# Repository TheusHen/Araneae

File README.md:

<table align="center">
<tr>
<td>

<h1>Araneae</h1>

</td>
<td>

</td>
</tr>
</table>

<h3 align="center">
Your network should answer to you, not report on you.
</h3>

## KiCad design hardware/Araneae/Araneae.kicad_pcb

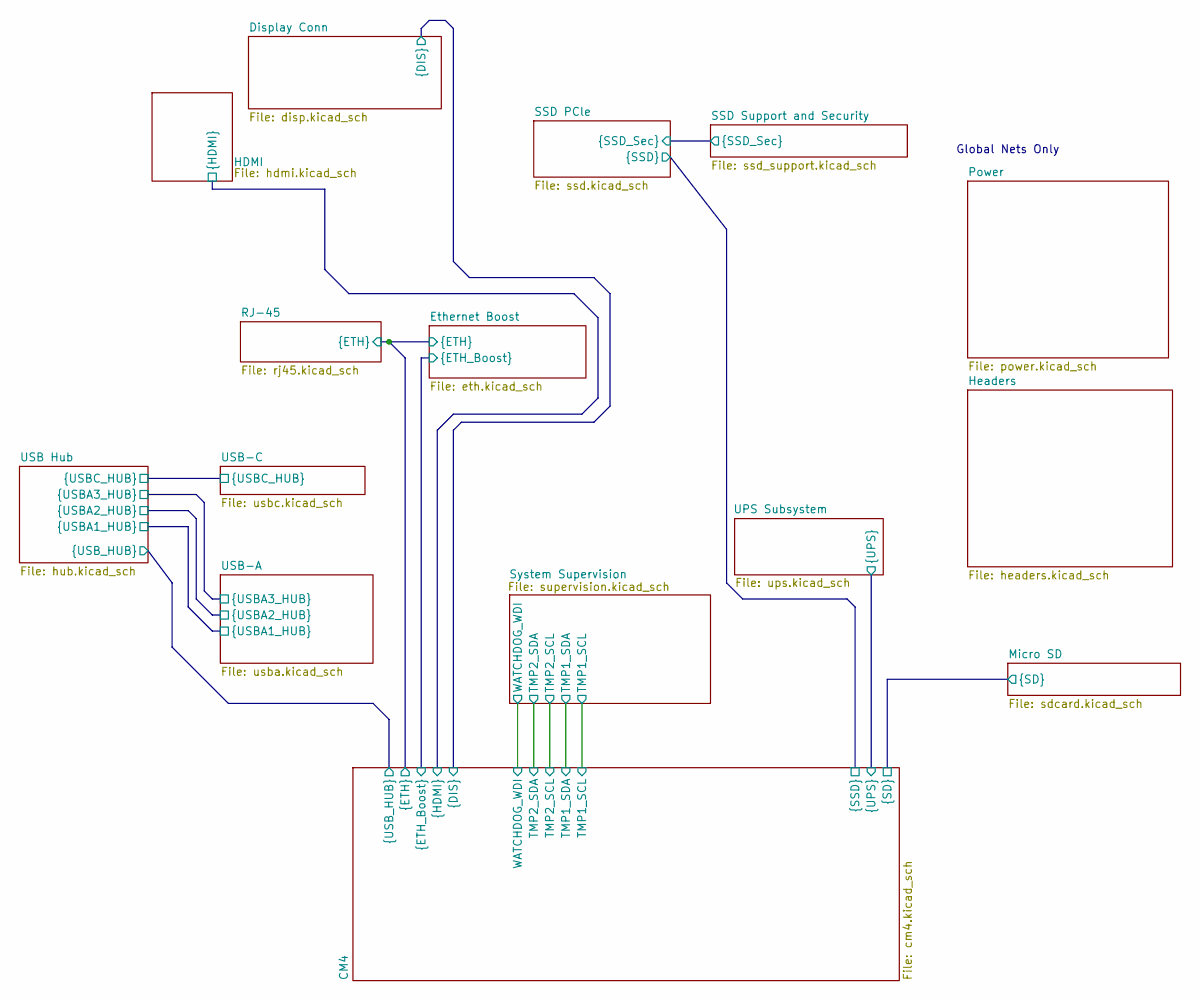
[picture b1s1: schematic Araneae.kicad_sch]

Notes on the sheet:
Global Nets Only

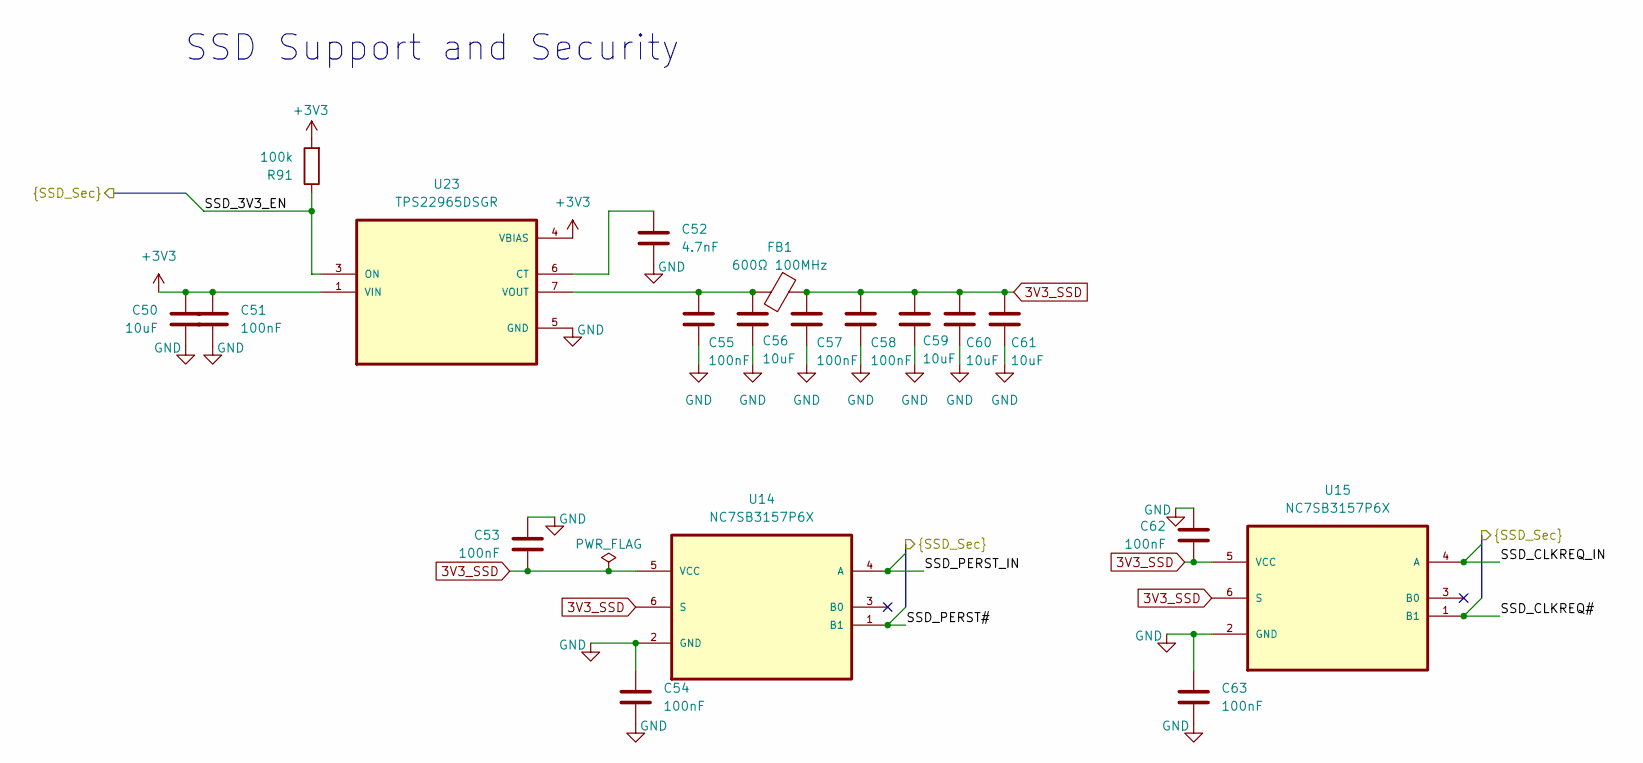
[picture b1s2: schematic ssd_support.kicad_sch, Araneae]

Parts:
C50, C56, C59: 10uF; C_0603_1608Metric
C51, C57, C62: 100nF; C_0805_2012Metric
C52: 4.7nF; C_0603_1608Metric
C53, C54, C55, C58, C63: 100nF; C_0603_1608Metric
C60, C61: 10uF; C_0805_2012Metric
FB1: 600Ω 100MHz; L_0805_2012Metric
R91: 100k; R_0603_1608Metric
U14, U15: NC7SB3157P6X; SOT65P210X110-6N; MPN NC7SB3157P6X
U23: TPS22965DSGR; SON50P200X200X80-9N

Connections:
3V3_SSD: C53.2, C57.1, C58.1, C59.1, C60.1, C61.1, C62.2, FB1.1, U14.5 (VCC), U14.6 (S), U15.5 (VCC), U15.6 (S); also elsewhere on the board
+3V3: C50.1, C51.1, R91.2, U23.1 (VIN), U23.2 (VIN), U23.4 (VBIAS); also elsewhere on the board
/SSD PCle/SSD_3V3_EN: R91.1, U23.3 (ON)
/SSD PCle/SSD_CLKREQ#: U15.1 (B1); also elsewhere on the board
/SSD PCle/SSD_CLKREQ_IN: U15.4 (A)
/SSD PCle/SSD_PERST#: U14.1 (B1); also elsewhere on the board
/SSD PCle/SSD_PERST_IN: U14.4 (A)
GND: C50.2, C51.2, C52.2, C53.1, C54.1, C54.2, C55.2, C56.2, C57.2, C58.2, C59.2, C60.2, C61.2, C62.1, C63.1, C63.2, U14.2 (GND), U15.2 (GND), U23.5 (GND), U23.9 (GND), U23.9_1 (GND), U23.9_2 (GND); also elsewhere on the board
unnamed: C55.1, C56.1, FB1.2, U23.7 (VOUT), U23.8 (VOUT)
unnamed: C52.1, U23.6 (CT)

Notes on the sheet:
SSD Support and Security

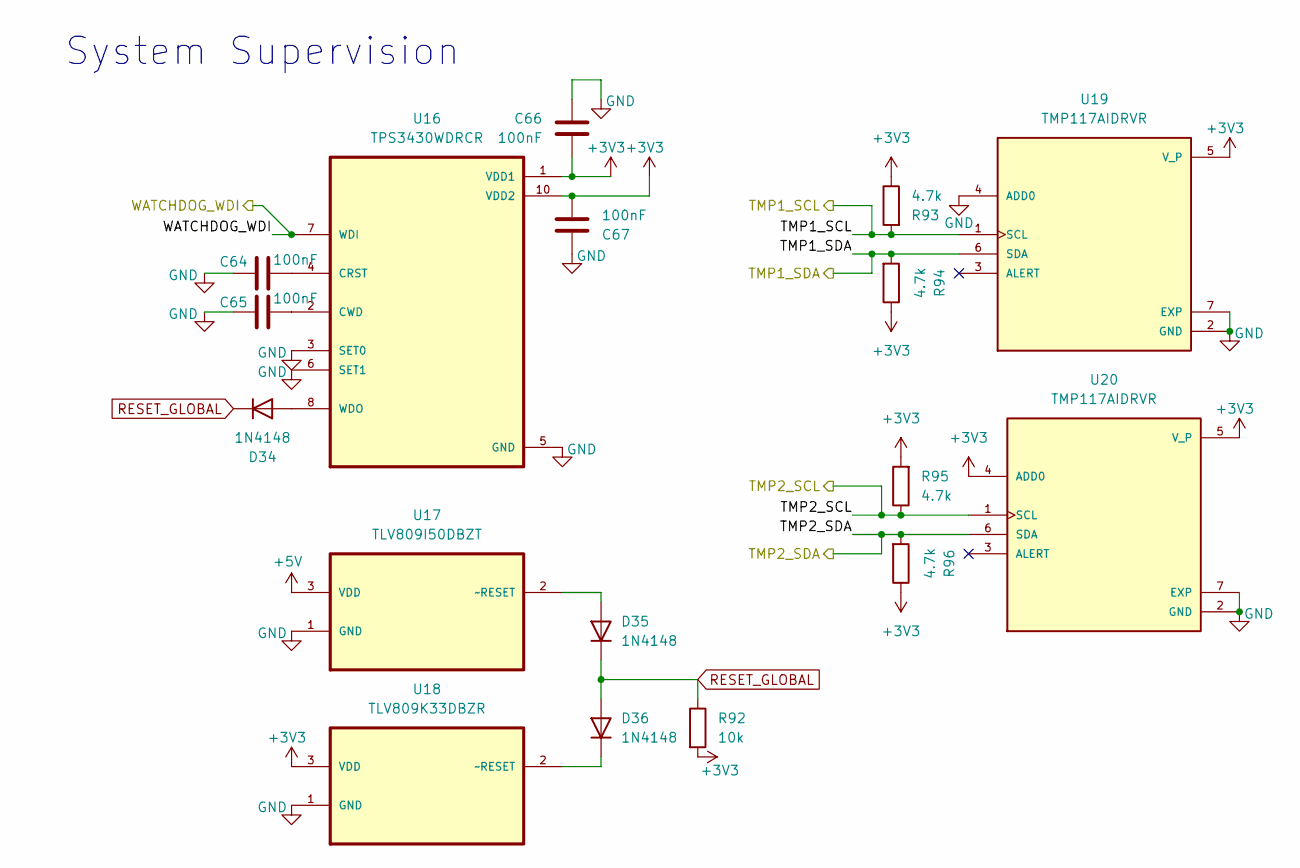
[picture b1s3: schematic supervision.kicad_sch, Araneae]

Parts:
C64, C65, C66, C67: 100nF; C_0603_1608Metric
D34, D35, D36: 1N4148; D_DO-35_SOD27_P7.62mm_Horizontal
R92: 10k; R_0603_1608Metric
R93, R94, R95, R96: 4.7k; R_0603_1608Metric
U16: TPS3430WDRCR; VREG_V62_16624-01YE
U17: TLV809I50DBZT; SOT95P280X145-3N; MPN TLV809I50DBZT
U18: TLV809K33DBZR; SOT95P280X145-3N; MPN TLV809K33DBZR
U19, U20: TMP117AIDRVR; SON65P200X200X80-7N; PARTREV B

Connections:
+3V3: C66.1, C67.1, R92.2, R93.1, R94.1, R95.2, R96.1, U16.1 (VDD1), U16.10 (VDD2), U18.3 (VDD), U19.5 (V_P), U20.4 (ADD0), U20.5 (V_P); also elsewhere on the board
+5V: U17.3 (VDD); also elsewhere on the board
/CM4/WATCHDOG_WDI: U16.7 (WDI); also elsewhere on the board
EXT_I2C_SCL: R93.2, R95.1, U19.1 (SCL), U20.1 (SCL); also elsewhere on the board
EXT_I2C_SDA: R94.2, R96.2, U19.6 (SDA), U20.6 (SDA); also elsewhere on the board
GND: C64.2, C65.2, C66.2, C67.2, U16.3 (SET0), U16.5 (GND), U16.6 (SET1), U17.1 (GND), U18.1 (GND), U19.2 (GND), U19.4 (ADD0), U19.7 (EXP), U20.2 (GND), U20.7 (EXP); also elsewhere on the board
unnamed: D34.2 (A), U16.8 (WDO)
unnamed: D35.2 (A), U17.2 (~RESET)
unnamed: D36.1 (K), U18.2 (~RESET)
unnamed: C64.1, U16.4 (CRST)
unnamed: C65.1, U16.2 (CWD)
RESET_GLOBAL: D34.1 (K), D35.1 (K), D36.2 (A), R92.1; also elsewhere on the board

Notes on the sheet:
System Supervision

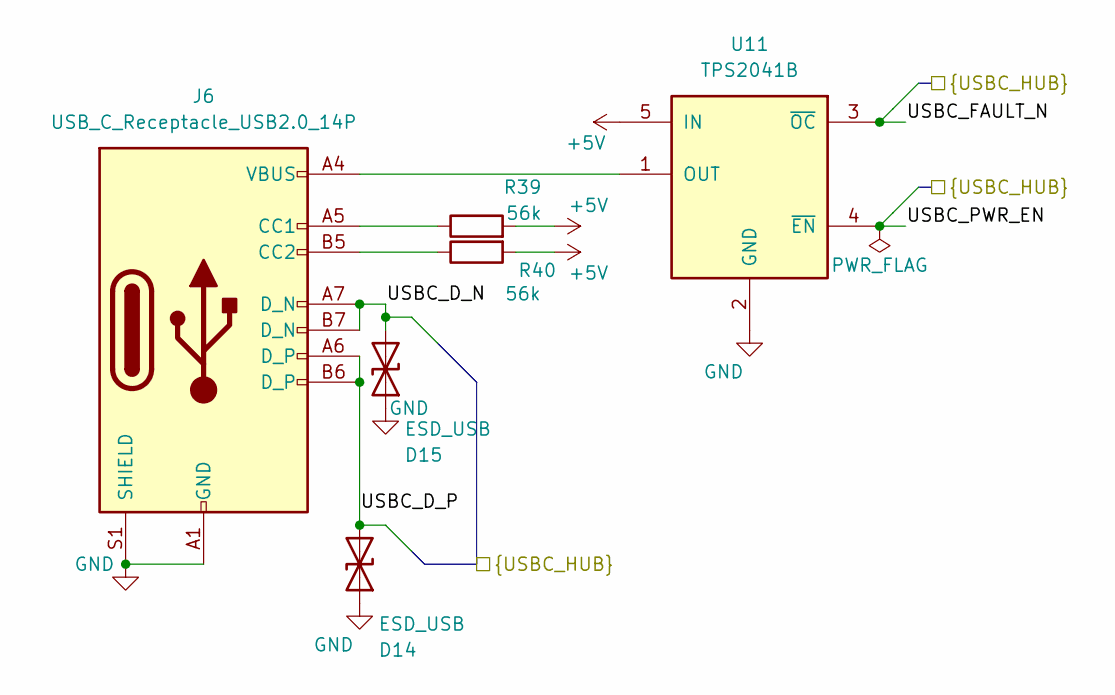
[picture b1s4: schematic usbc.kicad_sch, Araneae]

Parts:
D14, D15: ESD_USB; D_SOD-323
J6: USB_C_Receptacle_USB2.0_14P; USB_C_Receptacle_HRO_TYPE-C-31-M-12
R39, R40: 56k; R_0603_1608Metric
U11: TPS2041B; SOT-23-5

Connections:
+5V: R39.2, R40.2, U11.5 (IN); also elsewhere on the board
/USB Hub/USBC_D_N: D15.2 (A2), J6.A7 (D_N), J6.B7 (D_N); also elsewhere on the board
/USB Hub/USBC_D_P: D14.2 (A2), J6.A6 (D_P), J6.B6 (D_P); also elsewhere on the board
/USB Hub/USBC_FAULT_N: U11.3 (~OC); also elsewhere on the board
/USB Hub/USBC_PWR_EN: U11.4 (~EN); also elsewhere on the board
GND: D14.1 (A1), D15.1 (A1), J6.A1 (GND), J6.A12 (GND), J6.B1 (GND), J6.B12 (GND), J6.S1 (SHIELD), U11.2 (GND); also elsewhere on the board
unnamed: J6.A5 (CC1), R39.1
unnamed: J6.B5 (CC2), R40.1
unnamed: J6.A4 (VBUS), J6.A9 (VBUS), J6.B4 (VBUS), J6.B9 (VBUS), U11.1 (OUT)

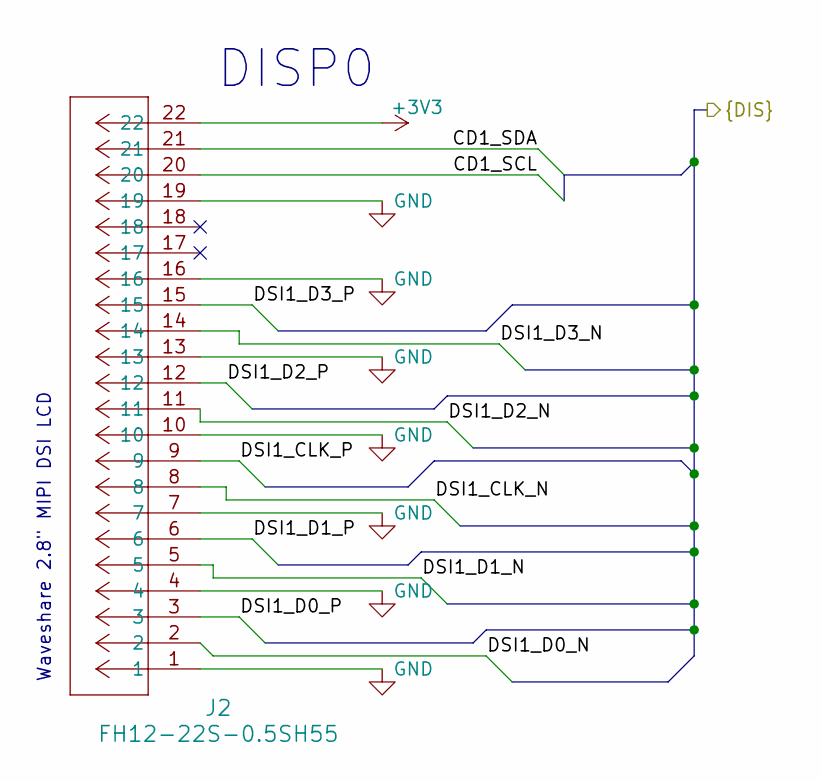
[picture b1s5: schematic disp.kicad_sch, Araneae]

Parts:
J2: FH12-22S-0.5SH55; CONN_FH12-22S-0.5SH55_HIR

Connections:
+3V3: J2.22; also elsewhere on the board
/CM4/CD1_SCL: J2.20; also elsewhere on the board
/CM4/CD1_SDA: J2.21; also elsewhere on the board
/CM4/DSI1_CLK_N: J2.8; also elsewhere on the board
/CM4/DSI1_CLK_P: J2.9; also elsewhere on the board
/CM4/DSI1_D0_N: J2.2; also elsewhere on the board
/CM4/DSI1_D0_P: J2.3; also elsewhere on the board
/CM4/DSI1_D1_N: J2.5; also elsewhere on the board
/CM4/DSI1_D1_P: J2.6; also elsewhere on the board
/CM4/DSI1_D2_N: J2.11; also elsewhere on the board
/CM4/DSI1_D2_P: J2.12; also elsewhere on the board
/CM4/DSI1_D3_N: J2.14; also elsewhere on the board
/CM4/DSI1_D3_P: J2.15; also elsewhere on the board
GND: J2.1, J2.4, J2.7, J2.10, J2.13, J2.16, J2.19; also elsewhere on the board

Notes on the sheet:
DISP0
Waveshare 2.8" MIPI DSI LCD

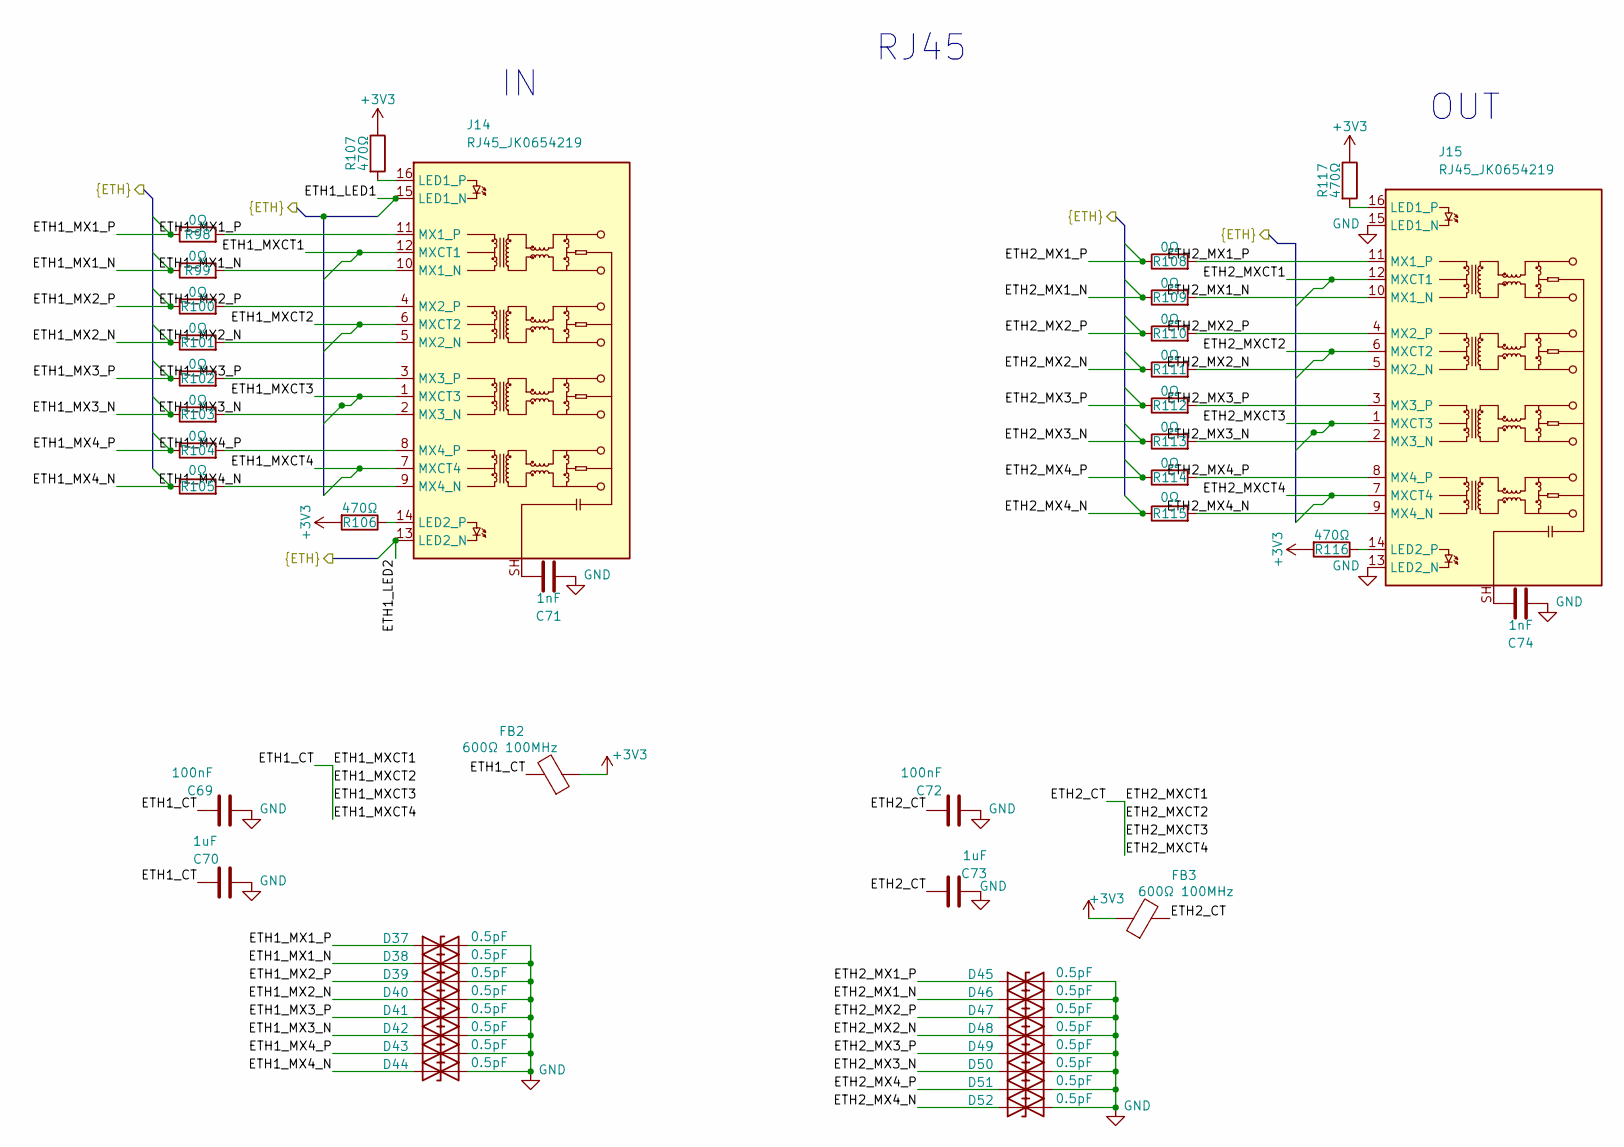
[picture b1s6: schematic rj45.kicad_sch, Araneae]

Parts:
C69: 100nF; C_0805_2012Metric
C70, C73: 1uF; C_0603_1608Metric
C71, C74: 1nF; C_0603_1608Metric
C72: 100nF; C_0603_1608Metric
D37, D38, D39, D40, D41, D42, D43, D44, D45, D46, D47, D48, D49, D50, D51, D52: 0.5pF; D_SOD-523
FB2, FB3: 600Ω 100MHz; L_0805_2012Metric
J14, J15: RJ45_JK0654219; RJ45_Pulse_JK0654219NL_Horizontal
R98, R99, R100, R101, R102, R103, R104, R105, R108, R109, R110, R111, R112, R113, R114, R115: 0Ω; R_0603_1608Metric
R106, R107, R116, R117: 470Ω; R_0603_1608Metric

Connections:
+3V3: FB2.1, FB3.1, R106.2, R107.1, R116.2, R117.1; also elsewhere on the board
/CM4/ETH1_LED1: J14.15 (LED1_N); also elsewhere on the board
/CM4/ETH1_LED2: J14.13 (LED2_N); also elsewhere on the board
/CM4/ETH1_MX1_N: D38.1 (A1), J14.10 (MX1_N), R99.1, R99.2; also elsewhere on the board
/CM4/ETH1_MX1_P: D37.1 (A1), J14.11 (MX1_P), R98.1, R98.2; also elsewhere on the board
/CM4/ETH1_MX2_N: D40.1 (A1), J14.5 (MX2_N), R101.1, R101.2; also elsewhere on the board
/CM4/ETH1_MX2_P: D39.1 (A1), J14.4 (MX2_P), R100.1, R100.2; also elsewhere on the board
/CM4/ETH1_MX3_N: D42.1 (A1), J14.2 (MX3_N), R103.1, R103.2; also elsewhere on the board
/CM4/ETH1_MX3_P: D41.1 (A1), J14.3 (MX3_P), R102.1, R102.2; also elsewhere on the board
/CM4/ETH1_MX4_N: D44.1 (A1), J14.9 (MX4_N), R105.1, R105.2; also elsewhere on the board
/CM4/ETH1_MX4_P: D43.1 (A1), J14.8 (MX4_P), R104.1, R104.2; also elsewhere on the board
/CM4/ETH1_MXCT4: C69.1, C70.2, FB2.2, J14.1 (MXCT3), J14.6 (MXCT2), J14.7 (MXCT4), J14.12 (MXCT1)
/CM4/ETH2_MX1_N: D46.1 (A1), J15.10 (MX1_N), R109.1, R109.2; also elsewhere on the board
/CM4/ETH2_MX1_P: D45.1 (A1), J15.11 (MX1_P), R108.1, R108.2; also elsewhere on the board
/CM4/ETH2_MX2_N: D48.1 (A1), J15.5 (MX2_N), R111.1, R111.2; also elsewhere on the board
/CM4/ETH2_MX2_P: D47.1 (A1), J15.4 (MX2_P), R110.1, R110.2; also elsewhere on the board
/CM4/ETH2_MX3_N: D50.1 (A1), J15.2 (MX3_N), R113.1, R113.2; also elsewhere on the board
/CM4/ETH2_MX3_P: D49.1 (A1), J15.3 (MX3_P), R112.1, R112.2; also elsewhere on the board
/CM4/ETH2_MX4_N: D52.1 (A1), J15.9 (MX4_N), R115.1, R115.2; also elsewhere on the board
/CM4/ETH2_MX4_P: D51.1 (A1), J15.8 (MX4_P), R114.1, R114.2; also elsewhere on the board
/CM4/ETH2_MXCT4: C72.1, C73.1, FB3.2, J15.1 (MXCT3), J15.6 (MXCT2), J15.7 (MXCT4), J15.12 (MXCT1)
GND: C69.2, C70.1, C71.2, C72.2, C73.2, C74.2, D37.2 (A2), D38.2 (A2), D39.2 (A2), D40.2 (A2), D41.2 (A2), D42.2 (A2), D43.2 (A2), D44.2 (A2), D45.2 (A2), D46.2 (A2), D47.2 (A2), D48.2 (A2), D49.2 (A2), D50.2 (A2), D51.2 (A2), D52.2 (A2), J15.13 (LED2_N), J15.15 (LED1_N); also elsewhere on the board
unnamed: C71.1, J14.SH
unnamed: C74.1, J15.SH
unnamed: J14.16 (LED1_P), R107.2
unnamed: J14.14 (LED2_P), R106.1
unnamed: J15.16 (LED1_P), R117.2
unnamed: J15.14 (LED2_P), R116.1

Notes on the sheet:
OUT
RJ45

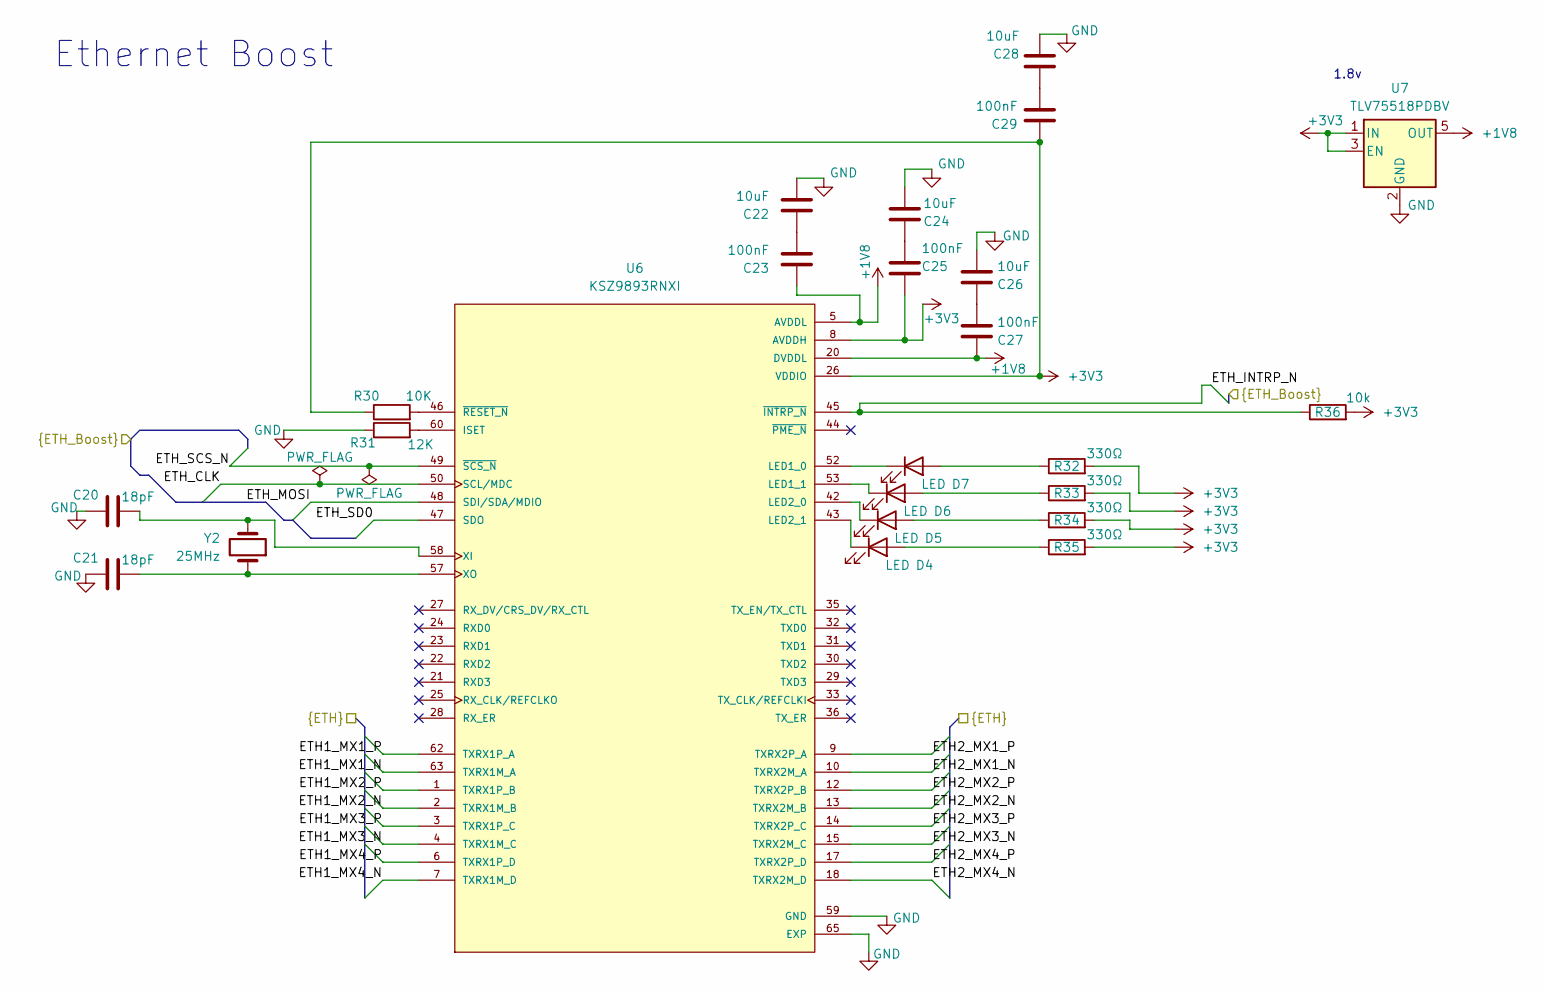
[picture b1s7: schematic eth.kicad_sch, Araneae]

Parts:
C20, C21: 18pF; C_0603_1608Metric
C22, C24, C26, C28: 10uF; C_0805_2012Metric
C23, C25, C27, C29: 100nF; C_0603_1608Metric
D4, D5, D6, D7: LED; LED_0805_2012Metric
R30: 10K; R_0603_1608Metric
R31: 12K; R_0603_1608Metric
R32, R33, R34, R35: 330Ω; R_0603_1608Metric
R36: 10k; R_0603_1608Metric
U6: KSZ9893RNXI; QFN40P800X800X90-65N; PARTREV C
U7: TLV75518PDBV; SOT-23-5
Y2: 25MHz; Crystal_SMD_3225-4Pin_3.2x2.5mm

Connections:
+1V8: C23.1, C27.1, U6.5 (AVDDL), U6.11 (AVDDL), U6.16 (AVDDL), U6.20 (DVDDL), U6.34 (DVDDL), U6.37 (DVDDL), U6.41 (DVDDL), U6.51 (DVDDL), U6.55 (DVDDL), U6.56 (AVDDL), U6.64 (AVDDL), U7.5 (OUT); also elsewhere on the board
+3V3: C25.1, C29.1, R30.1, R32.2, R33.2, R34.2, R35.2, R36.2, U6.8 (AVDDH), U6.19 (AVDDH), U6.26 (VDDIO), U6.38 (VDDIO), U6.54 (VDDIO), U6.61 (AVDDH), U7.1 (IN), U7.3 (EN); also elsewhere on the board
/CM4/ETH1_MX1_N: U6.63 (TXRX1M_A); also elsewhere on the board
/CM4/ETH1_MX1_P: U6.62 (TXRX1P_A); also elsewhere on the board
/CM4/ETH1_MX2_N: U6.2 (TXRX1M_B); also elsewhere on the board
/CM4/ETH1_MX2_P: U6.1 (TXRX1P_B); also elsewhere on the board
/CM4/ETH1_MX3_N: U6.4 (TXRX1M_C); also elsewhere on the board
/CM4/ETH1_MX3_P: U6.3 (TXRX1P_C); also elsewhere on the board
/CM4/ETH1_MX4_N: U6.7 (TXRX1M_D); also elsewhere on the board
/CM4/ETH1_MX4_P: U6.6 (TXRX1P_D); also elsewhere on the board
/CM4/ETH2_MX1_N: U6.10 (TXRX2M_A); also elsewhere on the board
/CM4/ETH2_MX1_P: U6.9 (TXRX2P_A); also elsewhere on the board
/CM4/ETH2_MX2_N: U6.13 (TXRX2M_B); also elsewhere on the board
/CM4/ETH2_MX2_P: U6.12 (TXRX2P_B); also elsewhere on the board
/CM4/ETH2_MX3_N: U6.15 (TXRX2M_C); also elsewhere on the board
/CM4/ETH2_MX3_P: U6.14 (TXRX2P_C); also elsewhere on the board
/CM4/ETH2_MX4_N: U6.18 (TXRX2M_D); also elsewhere on the board
/CM4/ETH2_MX4_P: U6.17 (TXRX2P_D); also elsewhere on the board
/CM4/ETH_INTRP_N: R36.1, U6.45 (~INTRP_N); also elsewhere on the board
/CM4/ETH_SCS_N: U6.49 (~SCS_N); also elsewhere on the board
EXT_SPI_MISO: U6.47 (SDO); also elsewhere on the board
EXT_SPI_MOSI: U6.48 (SDI/SDA/MDIO); also elsewhere on the board
EXT_SPI_SCLK: U6.50 (SCL/MDC); also elsewhere on the board
GND: C20.1, C21.1, C22.2, C24.2, C26.2, C28.2, R31.1, U6.59 (GND), U6.65 (EXP), U6.65_1 (EXP), U6.65_2 (EXP), U6.65_3 (EXP), U6.65_4 (EXP), U6.65_5 (EXP), U6.65_6 (EXP), U6.65_7 (EXP), U6.65_8 (EXP), U6.65_9 (EXP), U6.65_10 (EXP), U6.65_11 (EXP), U6.65_12 (EXP), U6.65_13 (EXP), U6.65_14 (EXP), U6.65_15 (EXP), U6.65_16 (EXP), U6.65_17 (EXP), U6.65_18 (EXP), U6.65_19 (EXP), U6.65_20 (EXP), U6.65_21 (EXP), U6.65_22 (EXP), U6.65_23 (EXP), U6.65_24 (EXP), U6.65_25 (EXP), U6.65_26 (EXP), U6.65_27 (EXP), U6.65_28 (EXP), U6.65_29 (EXP), U6.65_30 (EXP), U6.65_31 (EXP), U6.65_32 (EXP), U6.65_33 (EXP), U6.65_34 (EXP), U6.65_35 (EXP), U6.65_36 (EXP), U7.2 (GND); also elsewhere on the board
unnamed: C22.1, C23.2
unnamed: C24.1, C25.2
unnamed: C26.1, C27.2
unnamed: C28.1, C29.2
unnamed: D4.2 (A), R35.1
unnamed: D4.1 (K), U6.43 (LED2_1)
unnamed: D5.2 (A), R34.1
unnamed: D5.1 (K), U6.42 (LED2_0)
unnamed: D6.2 (A), R33.1
unnamed: D6.1 (K), U6.53 (LED1_1)
unnamed: D7.2 (A), R32.1
unnamed: D7.1 (K), U6.52 (LED1_0)
unnamed: R31.2, U6.60 (ISET)
unnamed: C20.2, U6.58 (XI), Y2.2
unnamed: C21.2, U6.57 (XO), Y2.1
unnamed: R30.2, U6.46 (~RESET_N)

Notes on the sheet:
Ethernet Boost
1.8v

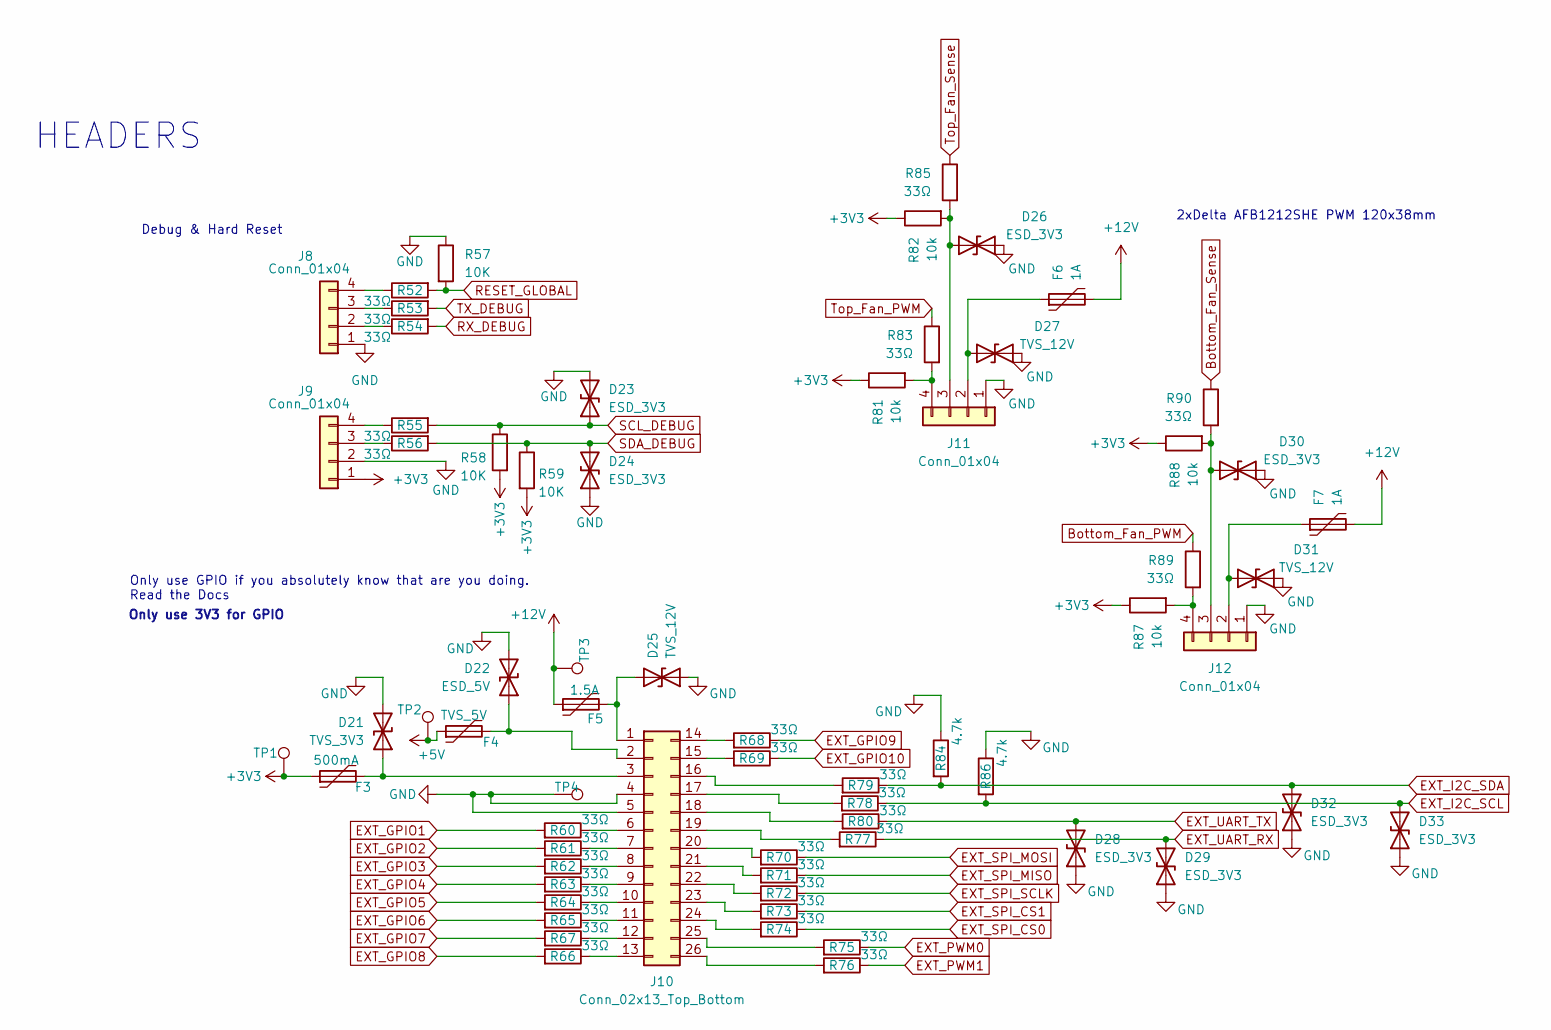
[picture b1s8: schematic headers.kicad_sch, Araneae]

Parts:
D21: TVS_3V3; D_SOD-323
D22: ESD_5V; D_SOD-323
D23, D24, D26, D28, D29, D30, D32, D33: ESD_3V3; D_SOD-323
D25, D27, D31: TVS_12V; D_SMF
F3: 500mA; Fuse_1206_3216Metric
F4: TVS_5V; Fuse_1206_3216Metric
F5: 1.5A; Fuse_1812_4532Metric
F6, F7: 1A; Fuse_1812_4532Metric
J8, J9, J11, J12: Conn_01x04; PinHeader_1x04_P2.54mm_Vertical
J10: Conn_02x13_Top_Bottom; IDC-Header_2x13_P2.54mm_Horizontal
R52, R53, R54, R55, R56, R60, R61, R62, R63, R64, R65, R66, R67, R68, R69, R70, R71, R72, R73, R74, R75, R76, R77, R78, R79, R80, R83, R85, R89, R90: 33Ω; R_0603_1608Metric
R57, R58, R59: 10K; R_0603_1608Metric
R81, R82, R87, R88: 10k; R_0603_1608Metric
R84, R86: 4.7k; R_0603_1608Metric
TP1, TP2, TP3, TP4: TestPoint_Pad_D1.5mm

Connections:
+3V3: F3.1, J9.1, R58.2, R59.2, R81.1, R82.1, R87.1, R88.1, TP1.1 (1_1); also elsewhere on the board
+5V: F4.1, TP2.1 (1_1); also elsewhere on the board
+12V: F5.1, F6.2, F7.2, TP3.1 (1_1); also elsewhere on the board
Bottom_Fan_PWM: R89.1; also elsewhere on the board
Bottom_Fan_Sense: R90.1; also elsewhere on the board
EXT_GPIO1: R60.2; also elsewhere on the board
EXT_GPIO2: R61.2; also elsewhere on the board
EXT_GPIO3: R62.2; also elsewhere on the board
EXT_GPIO4: R63.2; also elsewhere on the board
EXT_GPIO5: R64.2; also elsewhere on the board
EXT_GPIO6: R65.2; also elsewhere on the board
EXT_GPIO7: R67.2; also elsewhere on the board
EXT_GPIO8: R66.2; also elsewhere on the board
EXT_GPIO9: R68.1; also elsewhere on the board
EXT_GPIO10: R69.1; also elsewhere on the board
EXT_I2C_SCL: D33.2 (A2), R78.1, R86.2; also elsewhere on the board
EXT_I2C_SDA: D32.2 (A2), R79.1, R84.2; also elsewhere on the board
EXT_PWM0: R75.1; also elsewhere on the board
EXT_PWM1: R76.1; also elsewhere on the board
EXT_SPI_CS0: R74.1; also elsewhere on the board
EXT_SPI_CS1: R73.1; also elsewhere on the board
EXT_SPI_MISO: R71.1; also elsewhere on the board
EXT_SPI_MOSI: R70.1; also elsewhere on the board
EXT_SPI_SCLK: R72.1; also elsewhere on the board
EXT_UART_RX: D29.2 (A2), R77.1; also elsewhere on the board
EXT_UART_TX: D28.2 (A2), R80.1; also elsewhere on the board
GND: D21.2 (A2), D22.2 (A2), D23.2 (A2), D24.1 (A1), D25.1 (A1), D26.1 (A1), D27.1 (A1), D28.1 (A1), D29.1 (A1), D30.1 (A1), D31.1 (A1), D32.1 (A1), D33.1 (A1), J8.1, J9.2, J10.4, J10.5, J11.1, J12.1, R57.1, R84.1, R86.1, TP4.1 (1_1); also elsewhere on the board
unnamed: D21.1 (A1), F3.2, J10.3
unnamed: D22.1 (A1), F4.2, J10.2
unnamed: D25.2 (A2), F5.2, J10.1
unnamed: D26.2 (A2), J11.3, R82.2, R85.2
unnamed: D27.2 (A2), F6.1, J11.2
unnamed: D30.2 (A2), J12.3, R88.2, R90.2
unnamed: D31.2 (A2), F7.1, J12.2
unnamed: J8.2, R54.1
unnamed: J8.3, R53.1
unnamed: J8.4, R52.1
unnamed: J9.3, R56.1
unnamed: J9.4, R55.1
unnamed: J10.6, R60.1
unnamed: J10.7, R61.1
unnamed: J10.8, R62.1
unnamed: J10.9, R63.1
unnamed: J10.10, R64.1
unnamed: J10.11, R65.1
unnamed: J10.12, R67.1
unnamed: J10.13, R66.1
unnamed: J10.14, R68.2
unnamed: J10.15, R69.2
unnamed: J10.16, R79.2
unnamed: J10.17, R78.2
unnamed: J10.18, R80.2
unnamed: J10.19, R77.2
unnamed: J10.20, R70.2
unnamed: J10.21, R71.2
unnamed: J10.22, R72.2
unnamed: J10.23, R73.2
unnamed: J10.24, R74.2
unnamed: J10.25, R75.2
unnamed: J10.26, R76.2
unnamed: J11.4, R81.2, R83.2
unnamed: J12.4, R87.2, R89.2
RESET_GLOBAL: R52.2, R57.2; also elsewhere on the board
RX_DEBUG: R54.2; also elsewhere on the board
SCL_DEBUG: D23.1 (A1), R55.2, R58.1; also elsewhere on the board
SDA_DEBUG: D24.2 (A2), R56.2, R59.1; also elsewhere on the board
TX_DEBUG: R53.2; also elsewhere on the board
Top_Fan_PWM: R83.1; also elsewhere on the board
Top_Fan_Sense: R85.1; also elsewhere on the board

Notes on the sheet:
Only use GPIO if you absolutely know that are you doing. Read the Docs
HEADERS
Debug & Hard Reset
2xDelta AFB1212SHE PWM 120x38mm
Only use 3V3 for GPIO

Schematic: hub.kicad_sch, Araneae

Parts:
C75, C76: 18pF; C_0603_1608Metric
C77, C78, C79, C80, C81, C82, C83: 100nF; C_0603_1608Metric
C84: 1nF; C_0603_1608Metric
R118: 10k; R_0603_1608Metric
R119: 12k; R_0603_1608Metric
TP5: SUSP_IND; TestPoint_Pad_D1.5mm
U22: USB2514B_M2; 36-SQFN-EXPOSED-PAD
Y3: 24MHz; Crystal_SMD_3225-4Pin_3.2x2.5mm

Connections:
+3V3: C77.2, C78.2, C79.2, C80.2, C81.2, C82.2, R118.1, U22.5 (VDDA33-1), U22.10 (VDDA33-2), U22.15 (VDD33IO), U22.23 (VDD33REG), U22.29 (VDDA33-3), U22.36 (VDDPLLREF); also elsewhere on the board
+5V: U22.27 (VBUS_DET); also elsewhere on the board
/CM4/CM4_USB_D_N: U22.30 (DM-UP); also elsewhere on the board
/CM4/CM4_USB_D_P: U22.31 (DP-UP); also elsewhere on the board
/CM4/USB_HUB_RESET_N: R118.2, U22.26 (~RESET); also elsewhere on the board
/USB Hub/USBA1_D_N: U22.1 (DM1); also elsewhere on the board
/USB Hub/USBA1_D_P: U22.2 (DP1); also elsewhere on the board
/USB Hub/USBA1_FAULT_N: U22.13 (OCS1); also elsewhere on the board
/USB Hub/USBA1_PWR_EN: U22.12 (PRTPWR1); also elsewhere on the board
/USB Hub/USBA2_D_N: U22.3 (DM2); also elsewhere on the board
/USB Hub/USBA2_D_P: U22.4 (DP2); also elsewhere on the board
/USB Hub/USBA2_FAULT_N: U22.17 (OCS2); also elsewhere on the board
/USB Hub/USBA2_PWR_EN: U22.16 (PRTPWR2); also elsewhere on the board
/USB Hub/USBA3_D_N: U22.6 (DM3); also elsewhere on the board
/USB Hub/USBA3_D_P: U22.7 (DP3); also elsewhere on the board
/USB Hub/USBA3_FAULT_N: U22.19 (OCS3); also elsewhere on the board
/USB Hub/USBA3_PWR_EN: U22.18 (PRTPWR3); also elsewhere on the board
/USB Hub/USBC_D_N: U22.8 (DM4); also elsewhere on the board
/USB Hub/USBC_D_P: U22.9 (DP4); also elsewhere on the board
/USB Hub/USBC_FAULT_N: U22.21 (OCS4); also elsewhere on the board
/USB Hub/USBC_PWR_EN: U22.20 (PRTPWR4); also elsewhere on the board
GND: C75.1, C76.1, C77.1, C78.1, C79.1, C80.1, C81.1, C82.1, C83.1, C84.1, R119.1, U22.11 (TEST), U22.22 (SMBDATA), U22.24 (SMBCLK), U22.25 (CFG_SEL1), U22.37 (VSS); also elsewhere on the board
unnamed: C84.2, U22.14 (CRFILT)
unnamed: C83.2, U22.34 (PLLFILT)
unnamed: R119.2, U22.35 (RBIAS)
unnamed: TP5.1 (1_1), U22.28 (SUSP_IND)
unnamed: C75.2, U22.32 (XTAL1), Y3.1
unnamed: C76.2, U22.33 (XTAL2), Y3.2

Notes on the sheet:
USB Hub

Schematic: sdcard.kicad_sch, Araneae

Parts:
C68: 10uF; C_0603_1608Metric
J13: Micro_SD_Card; microSD_HC_Hirose_DM3D-SF
R97: 12k; R_0603_1608Metric
U21: RT9742GGJ5; TSOT-23-5

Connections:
+3V3: R97.1, U21.P$5 (IN); also elsewhere on the board
/CM4/SD_CLK: J13.5 (CLK); also elsewhere on the board
/CM4/SD_DAT0: J13.7 (DAT0); also elsewhere on the board
/CM4/SD_DAT1: J13.8 (DAT1); also elsewhere on the board
/CM4/SD_DAT2: J13.1 (DAT2); also elsewhere on the board
/CM4/SD_DAT3: J13.2 (DAT3/CD); also elsewhere on the board
/CM4/SD_PWR: C68.1, J13.3 (CMD), J13.4 (VDD), U21.P$1 (OUT); also elsewhere on the board
/CM4/SD_PWR_ON: R97.2, U21.P$4 (EN); also elsewhere on the board
GND: C68.2, J13.6 (VSS), J13.9 (SHIELD), U21.P$2 (GND); also elsewhere on the board

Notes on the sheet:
MICRO SD

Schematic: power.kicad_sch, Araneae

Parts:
C32: 10µF; C_0805_2012Metric
C33, C35: 100nF; C_0805_2012Metric
C34: 10µF; C_0603_1608Metric
C36: 150pF; C_0603_1608Metric
C37: 220pF; C_0603_1608Metric
C38, C39, C45, C46: 100nF; C_0603_1608Metric
C40: 22µF; C_0603_1608Metric
C41: 22µF; C_1206_3216Metric
C42: 100nF; C_1206_3216Metric
C43: 47uF; C_0603_1608Metric
C44: 10nF; C_0805_2012Metric
C47: 10uF; C_0603_1608Metric
C48: 47uF; C_0805_2012Metric
C49: 1nF; C_0805_2012Metric
D16: SMF12A; D_SMF
D17, D18, D19, D20: SS34; D_SMA
F2: 3A; Fuse_1812_4532Metric
IC1, IC2: MP1584EN-LF-Z; SOIC127P600X170-9N; MOUSER_PART_NUMBER 946-MP1584ENLFZ
J7: Barrel_Jack; BarrelJack_CUI_PJ-102AH_Horizontal
L2: 15µH; L_7.3x7.3_H4.5
L3: 6.8µH; L_7.3x7.3_H4.5
L4: 22µH; L_10.4x10.4_H4.8
R41: 100k; R_0603_1608Metric
R42: 68k; R_0603_1608Metric
R43, R44: 193k; R_0603_1608Metric
R45, R46: 40,2k; R_0603_1608Metric
R47: 211k; R_0603_1608Metric
R48: 124k; R_0603_1608Metric
R49: 140k; R_0603_1608Metric
R50, R51: 10K; R_0603_1608Metric
U12: TPS54331DG4; SOIC127P599X175-8N

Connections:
12V_SYSTEM: C32.1, C34.1, C43.1, IC1.2 (EN), IC1.7 (VIN), IC2.2 (EN), IC2.7 (VIN), L4.2, R49.1; also elsewhere on the board
19V: C46.2, F2.1, U12.2 (VIN), U12.3 (EN); also elsewhere on the board
+3V3: C41.1, L3.2, R48.2; also elsewhere on the board
+5V: C40.1, L2.2, R47.2; also elsewhere on the board
GND: C33.2, C35.2, C36.2, C37.2, C40.2, C41.2, C42.2, C44.2, C48.1, C49.2, D16.2 (A2), D17.2 (A), D18.2 (A), D19.2 (A), D20.2 (A), IC1.5 (GND), IC1.9 (EP), IC2.5 (GND), IC2.9 (EP), J7.2, R43.2, R44.2, R45.1, R46.1, R50.2, U12.7 (GND); also elsewhere on the board
unnamed: C32.2, C33.1
unnamed: C34.2, C35.1
unnamed: C36.1, R41.2
unnamed: C37.1, R42.2
unnamed: C42.1, C43.2
unnamed: C46.1, C47.2
unnamed: C47.1, C48.2
unnamed: C49.1, R51.2
unnamed: D16.1 (A1), D17.1 (K), F2.2, J7.1
unnamed: C38.2, D18.1 (K), IC1.1 (SW), L2.1
unnamed: C39.2, D19.1 (K), IC2.1 (SW), L3.1
unnamed: C45.1, D20.1 (K), L4.1, U12.8 (PH)
unnamed: C38.1, IC1.8 (BST)
unnamed: IC1.3 (COMP), R41.1
unnamed: IC1.4 (FB), R45.2, R47.1
unnamed: IC1.6 (FREQ), R43.1
unnamed: C39.1, IC2.8 (BST)
unnamed: IC2.3 (COMP), R42.1
unnamed: IC2.4 (FB), R46.2, R48.1
unnamed: IC2.6 (FREQ), R44.1
unnamed: C45.2, U12.1 (BOOT)
unnamed: R51.1, U12.6 (COMP)
unnamed: C44.1, U12.4 (SS)
unnamed: R49.2, R50.1, U12.5 (VSENSE)

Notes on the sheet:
12V
19V
3V3

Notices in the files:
README.md:
License: unlicense
